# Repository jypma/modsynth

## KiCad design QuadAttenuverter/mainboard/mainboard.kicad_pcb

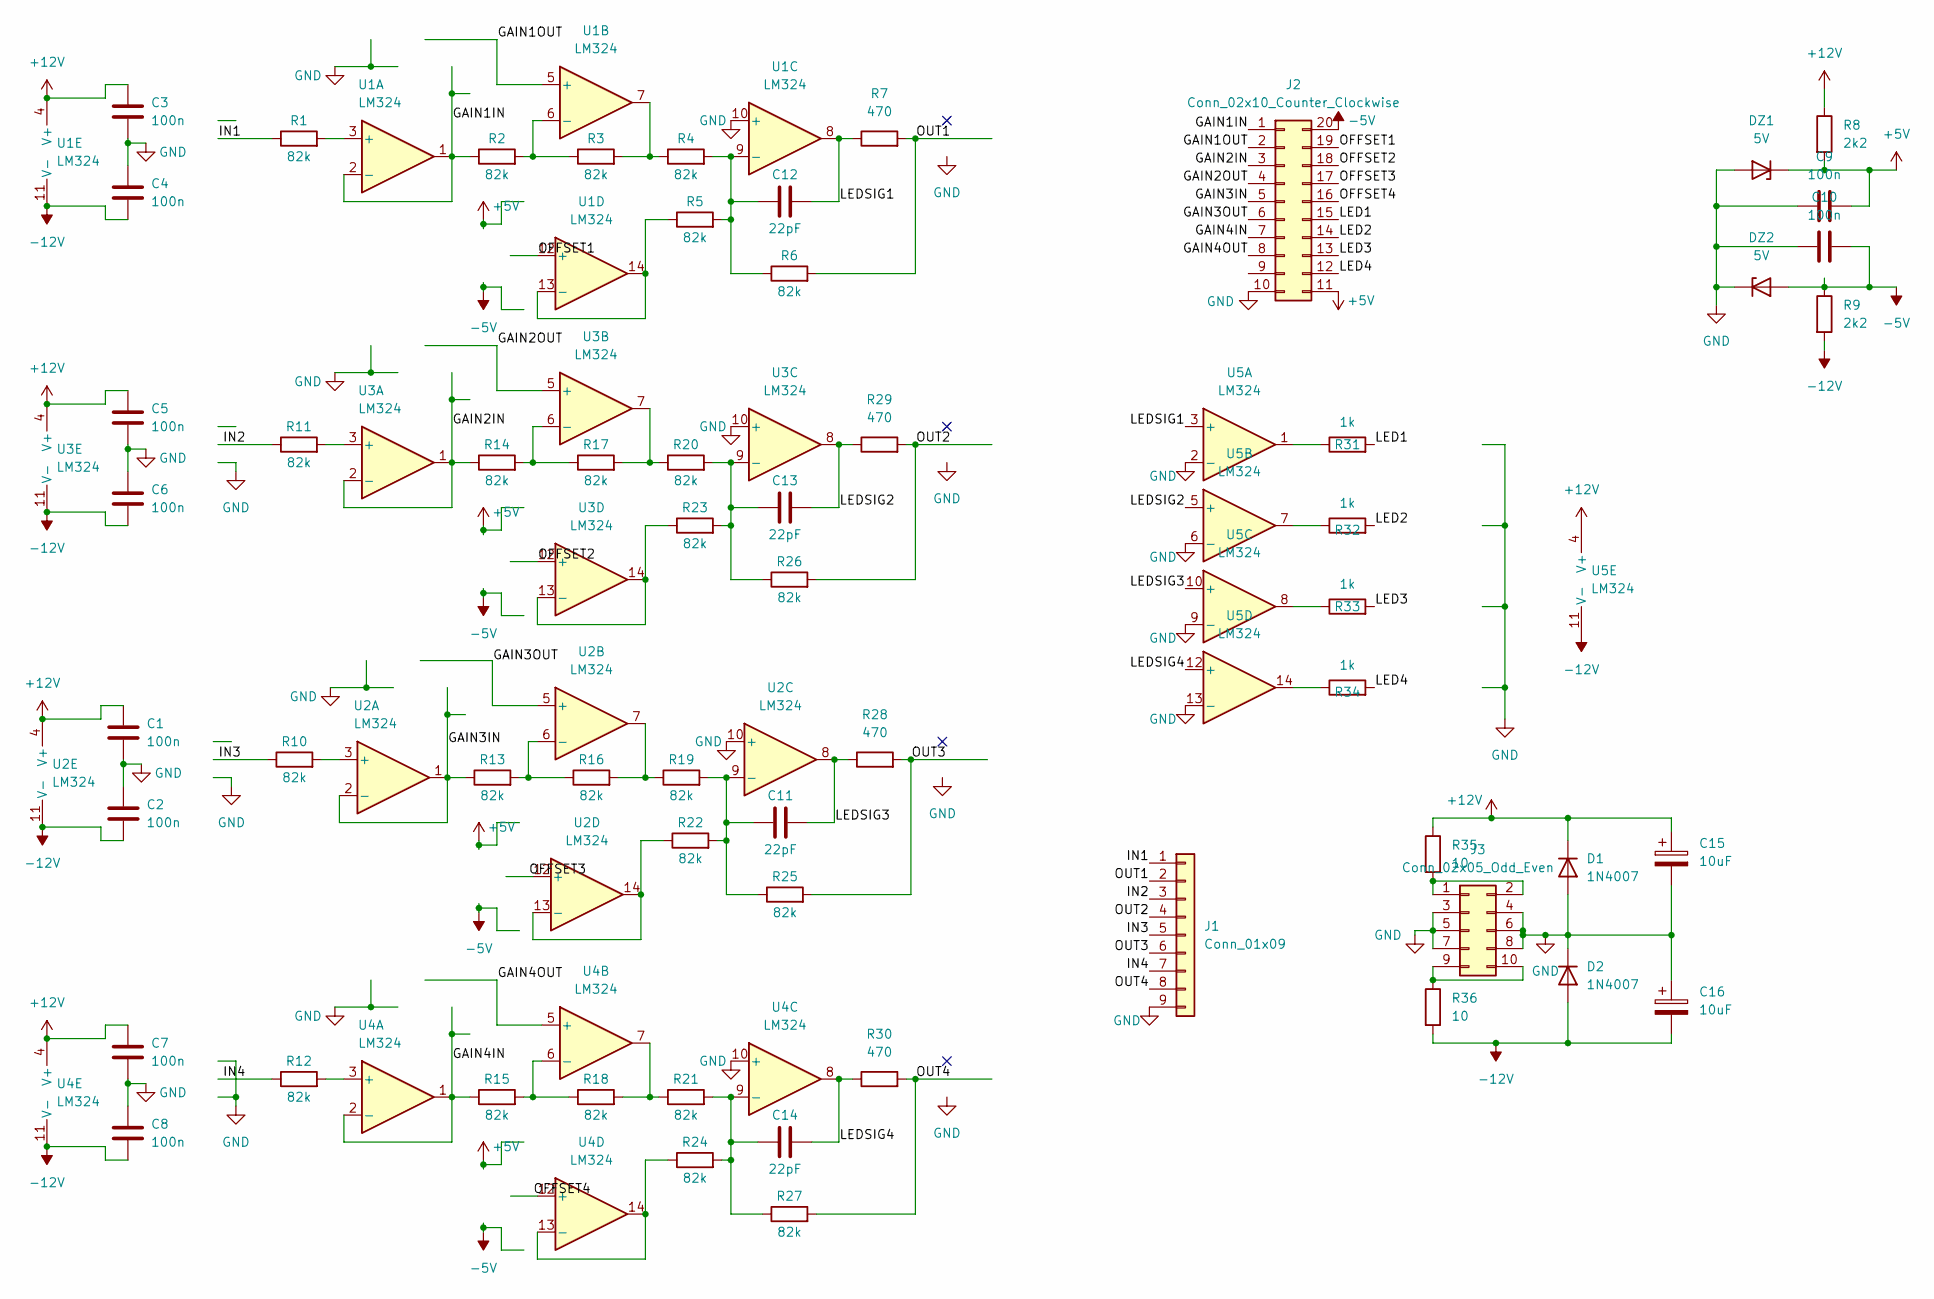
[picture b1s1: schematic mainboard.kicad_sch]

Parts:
C1, C2, C3, C4, C5, C6, C7, C8, C9, C10: 100n; C_0603_1608Metric_Pad1.08x0.95mm_HandSolder
C11, C12, C13, C14: 22pF; C_0603_1608Metric_Pad1.08x0.95mm_HandSolder
C15, C16: 10uF; CP_Radial_D5.0mm_P2.00mm
D1, D2: 1N4007; D_DO-41_SOD81_P7.62mm_Horizontal
DZ1, DZ2: 5V; D_DO-41_SOD81_P7.62mm_Horizontal
J1: Conn_01x09; PinHeader_1x09_P2.54mm_Vertical
J2: Conn_02x10_Counter_Clockwise; PinHeader_2x10_P2.54mm_Vertical
J3: Conn_02x05_Odd_Even; PinHeader_2x05_P2.54mm_Vertical
R1, R2, R3, R4, R5, R6, R10, R11, R12, R13, R14, R15, R16, R17, R18, R19, R20, R21, R22, R23, R24, R25, R26, R27: 82k; R_0603_1608Metric_Pad0.98x0.95mm_HandSolder
R7, R28, R29, R30: 470; R_0603_1608Metric_Pad0.98x0.95mm_HandSolder
R8, R9: 2k2; R_0603_1608Metric_Pad0.98x0.95mm_HandSolder
R31, R32, R33, R34: 1k; R_0603_1608Metric_Pad0.98x0.95mm_HandSolder
R35, R36: 10; R_0603_1608Metric_Pad0.98x0.95mm_HandSolder
U1, U2, U3, U4, U5: LM324; SO-14_3.9x8.65mm_P1.27mm

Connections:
+5V: C9.2, DZ1.1 (K), J2.11, R8.2
+12V: C1.1, C3.1, C5.1, C7.1, C15.1, D1.1 (K), R8.1, R35.1, U1.4 (V+), U2.4 (V+), U3.4 (V+), U4.4 (V+), U5.4 (V+)
-5V: C10.2, DZ2.2 (A), J2.20, R9.1
-12V: C2.2, C4.2, C6.2, C8.2, C16.2, D2.2 (A), R9.2, R36.2, U1.11 (V-), U2.11 (V-), U3.11 (V-), U4.11 (V-), U5.11 (V-)
/GAIN1IN: J2.1, R2.1, U1.1, U1.2 (-)
/GAIN1OUT: J2.2, U1.5 (+)
/GAIN2IN: J2.3, R14.1, U3.1, U3.2 (-)
/GAIN2OUT: J2.4, U3.5 (+)
/GAIN3IN: J2.5, R13.1, U2.1, U2.2 (-)
/GAIN3OUT: J2.6, U2.5 (+)
/GAIN4IN: J2.7, R15.1, U4.1, U4.2 (-)
/GAIN4OUT: J2.8, U4.5 (+)
/IN1: J1.1, R1.1
/IN2: J1.3, R11.1
/IN3: J1.5, R10.1
/IN4: J1.7, R12.1
/LED1: J2.15, R31.2
/LED2: J2.14, R32.2
/LED3: J2.13, R33.2
/LED4: J2.12, R34.2
/LEDSIG1: C12.2, R7.1, U1.8, U5.3 (+)
/LEDSIG2: C13.2, R29.1, U3.8, U5.5 (+)
/LEDSIG3: C11.2, R28.1, U2.8, U5.10 (+)
/LEDSIG4: C14.2, R30.1, U4.8, U5.12 (+)
/OFFSET1: J2.19, U1.12 (+)
/OFFSET2: J2.18, U3.12 (+)
/OFFSET3: J2.17, U2.12 (+)
/OFFSET4: J2.16, U4.12 (+)
/OUT1: J1.2, R6.2, R7.2
/OUT2: J1.4, R26.2, R29.2
/OUT3: J1.6, R25.2, R28.2
/OUT4: J1.8, R27.2, R30.2
GND: C1.2, C2.1, C3.2, C4.1, C5.2, C6.1, C7.2, C8.1, C9.1, C10.1, C15.2, C16.1, D1.2 (A), D2.1 (K), DZ1.2 (A), DZ2.1 (K), J1.9, J2.10, J3.3, J3.4, J3.5, J3.6, J3.7, J3.8, U1.10 (+), U2.10 (+), U3.10 (+), U4.10 (+), U5.2 (-), U5.6 (-), U5.9 (-), U5.13 (-)
unnamed: C11.1, R19.2, R22.2, R25.1, U2.9 (-)
unnamed: C12.1, R4.2, R5.2, R6.1, U1.9 (-)
unnamed: C13.1, R20.2, R23.2, R26.1, U3.9 (-)
unnamed: C14.1, R21.2, R24.2, R27.1, U4.9 (-)
unnamed: J3.1, J3.2, R35.2
unnamed: J3.9, J3.10, R36.1
unnamed: R1.2, U1.3 (+)
unnamed: R2.2, R3.1, U1.6 (-)
unnamed: R3.2, R4.1, U1.7
unnamed: R5.1, U1.13 (-), U1.14
unnamed: R10.2, U2.3 (+)
unnamed: R11.2, U3.3 (+)
unnamed: R12.2, U4.3 (+)
unnamed: R13.2, R16.1, U2.6 (-)
unnamed: R14.2, R17.1, U3.6 (-)
unnamed: R15.2, R18.1, U4.6 (-)
unnamed: R16.2, R19.1, U2.7
unnamed: R17.2, R20.1, U3.7
unnamed: R18.2, R21.1, U4.7
unnamed: R22.1, U2.13 (-), U2.14
unnamed: R23.1, U3.13 (-), U3.14
unnamed: R24.1, U4.13 (-), U4.14
unnamed: R31.1, U5.1
unnamed: R32.1, U5.7
unnamed: R33.1, U5.8
unnamed: R34.1, U5.14

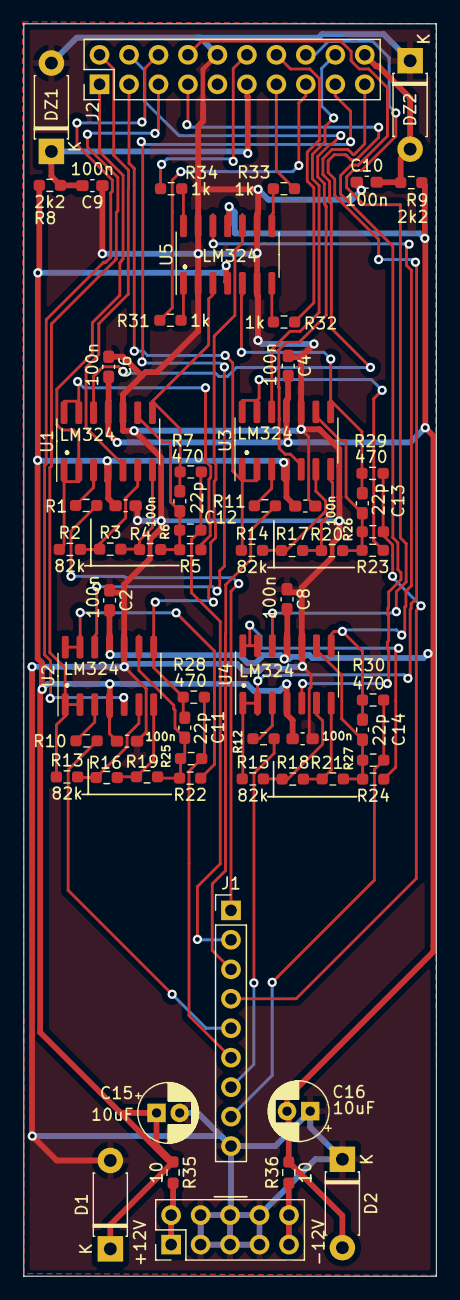
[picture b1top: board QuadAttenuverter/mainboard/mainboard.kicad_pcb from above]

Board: 2 copper layers, 35.6 x 108.0 mm, 64 parts (0 on the bottom side), 59 nets.

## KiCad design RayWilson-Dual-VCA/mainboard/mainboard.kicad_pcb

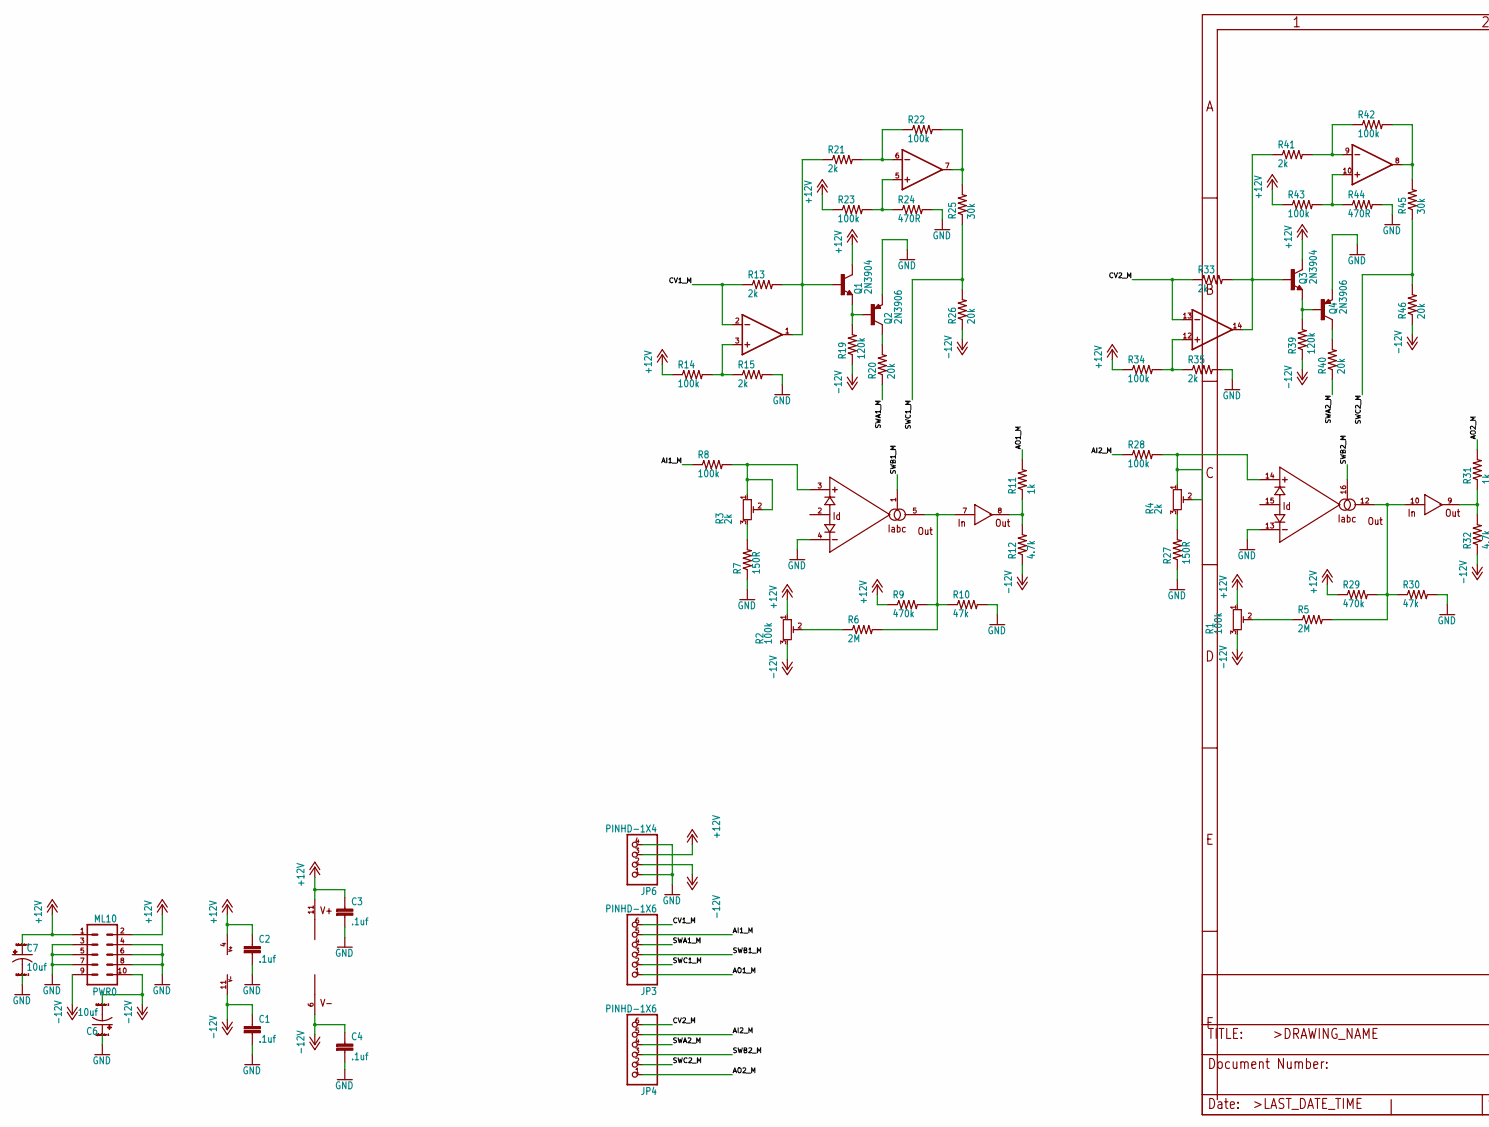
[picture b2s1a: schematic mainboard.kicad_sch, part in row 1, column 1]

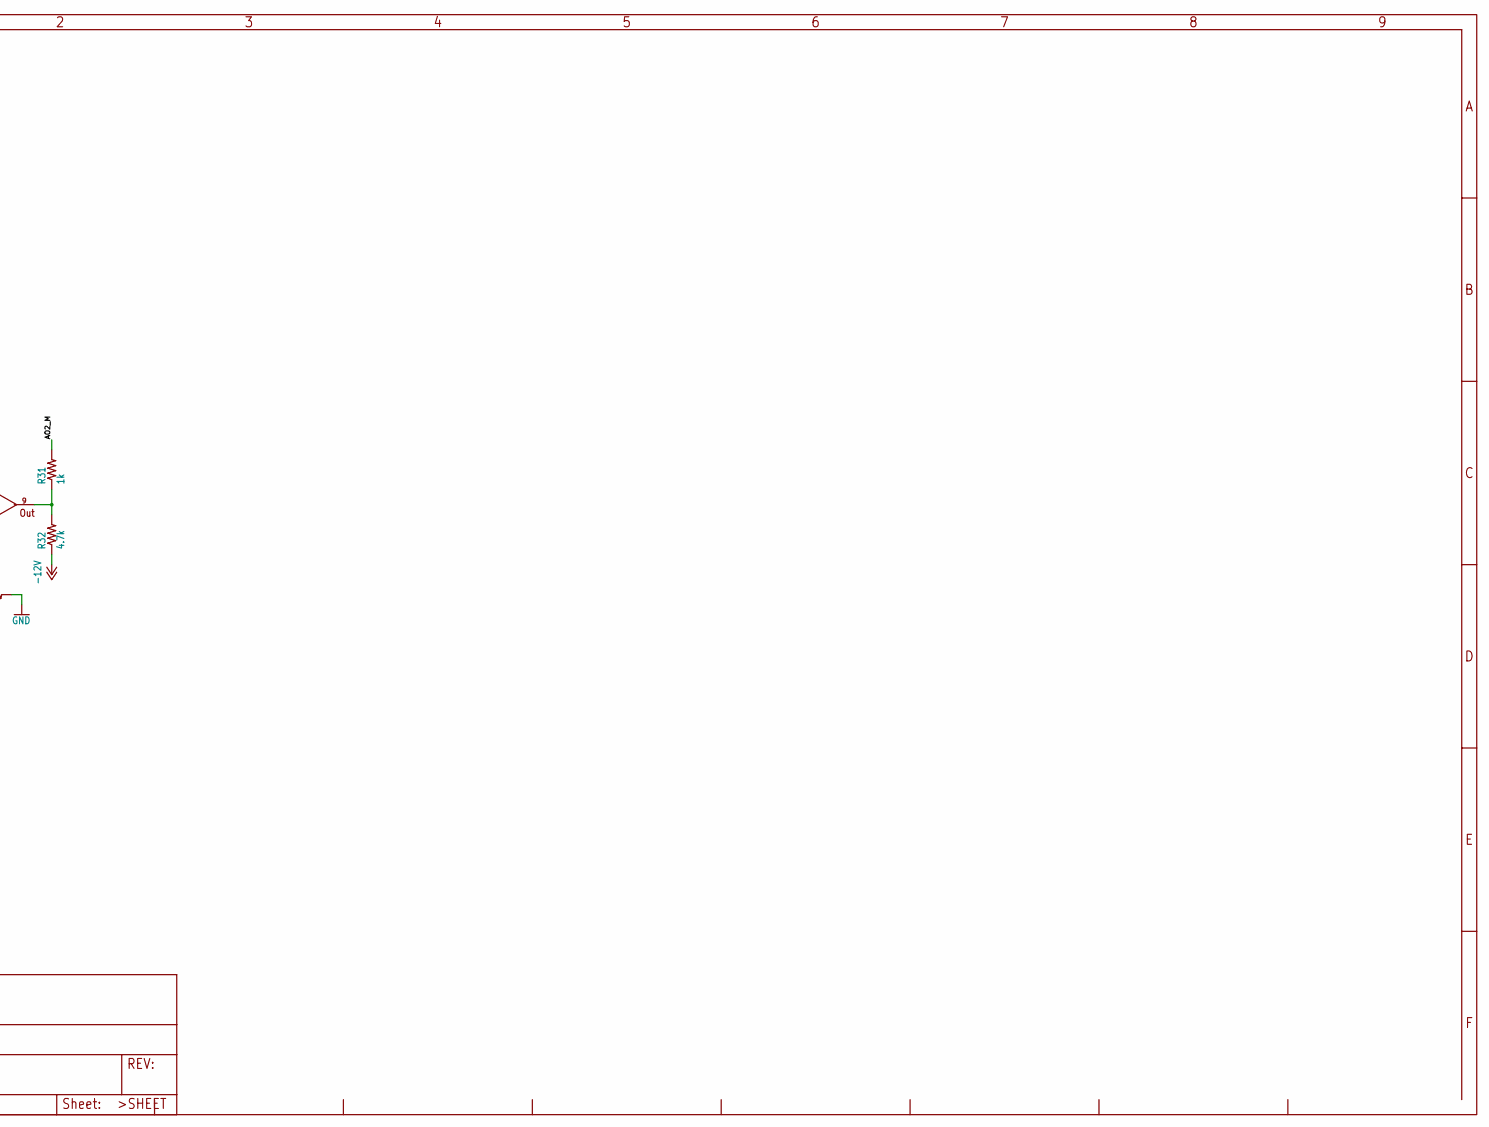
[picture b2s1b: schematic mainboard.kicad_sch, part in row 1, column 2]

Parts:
C1, C2, C3, C4: .1uf; C050-024X044
C6, C7: 10uf; E2,5-5
IC1: TL074P; SO-14_3.9x8.65mm_P1.27mm
IC2: LM13700N; SOIC-16_3.9x9.9mm_P1.27mm
JP3, JP4: PINHD-1X6; 1X06
JP6: PINHD-1X4; 1X04
PWR0: ML10
Q1, Q3: 2N3904; TO92
Q2, Q4: 2N3906; TO92
R1, R2: 100k; Potentiometer_Bourns_3296W_Vertical
R3, R4: 2k; Potentiometer_Bourns_3296W_Vertical
R5, R6: 2M; 0204_7
R7, R27: 150R; 0204_7
R8, R14, R22, R23, R28, R34, R42, R43: 100k; 0204_7
R9, R29: 470k; 0204_7
R10, R30: 47k; 0204_7
R11, R31: 1k; 0204_7
R12, R32: 4.7k; 0204_7
R13, R15, R21, R33, R35, R41: 2k; 0204_7
R19, R39: 120k; 0204_7
R20, R26, R40, R46: 20k; 0204_7
R24, R44: 470R; 0204_7
R25, R45: 30k; 0204_7

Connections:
+12V: C2.1, C3.1, C7.+, IC1.4 (V+), IC2.11 (V+), JP6.3, PWR0.1, PWR0.2, Q1.1 (C), Q3.1 (C), R1.1, R2.1, R9.1, R14.1, R23.1, R29.1, R34.1, R43.1
-12V: C1.1, C4.1, C6.-, IC1.11 (V-), IC2.6 (V-), JP6.2, PWR0.9, PWR0.10, R1.3, R2.3, R12.1, R19.1, R26.1, R32.1, R39.1, R46.1
/AI1_M: JP3.5, R8.1
/AI2_M: JP4.5, R28.1
/AO1_M: JP3.1, R11.2
/AO2_M: JP4.1, R31.2
/CV1_M: IC1.2 (-IN), JP3.6, R13.1
/CV2_M: IC1.13 (-IN), JP4.6, R33.1
/SWA1_M: JP3.4, R20.1
/SWA2_M: JP4.4, R40.1
/SWB1_M: IC2.1 (IABC), JP3.3
/SWB2_M: IC2.16 (IABC), JP4.3
/SWC1_M: JP3.2, R25.1, R26.2
/SWC2_M: JP4.2, R45.1, R46.2
GND: C1.2, C2.2, C3.2, C4.2, C6.+, C7.-, IC2.4 (-IN), IC2.13 (-IN), JP6.1, JP6.4, PWR0.3, PWR0.4, PWR0.5, PWR0.6, PWR0.7, PWR0.8, Q2.3 (E), Q4.3 (E), R7.1, R10.2, R15.2, R24.2, R27.1, R30.2, R35.2, R44.2
unnamed: IC1.1 (OUT), Q1.2 (B), R13.2, R21.1
unnamed: IC1.3 (+IN), R14.2, R15.1
unnamed: IC1.5 (+IN), R23.2, R24.1
unnamed: IC1.6 (-IN), R21.2, R22.1
unnamed: IC1.7 (OUT), R22.2, R25.2
unnamed: IC1.8 (OUT), R42.2, R45.2
unnamed: IC1.9 (-IN), R41.2, R42.1
unnamed: IC1.10 (+IN), R43.2, R44.1
unnamed: IC1.12 (+IN), R34.2, R35.1
unnamed: IC1.14 (OUT), Q3.2 (B), R33.2, R41.1
unnamed: IC2.3 (+IN), R3.1, R3.2, R8.2
unnamed: IC2.5 (OUT), IC2.7 (IN), R6.2, R9.2, R10.1
unnamed: IC2.8 (OUT), R11.1, R12.2
unnamed: IC2.9 (OUT), R31.1, R32.2
unnamed: IC2.10 (IN), IC2.12 (OUT), R5.2, R29.2, R30.1
unnamed: IC2.14 (+IN), R4.1, R4.2, R28.2
unnamed: Q1.3 (E), Q2.2 (B), R19.2
unnamed: Q2.1 (C), R20.2
unnamed: Q3.3 (E), Q4.2 (B), R39.2
unnamed: Q4.1 (C), R40.2
unnamed: R1.2, R5.1
unnamed: R2.2, R6.1
unnamed: R3.3, R7.2
unnamed: R4.3, R27.2

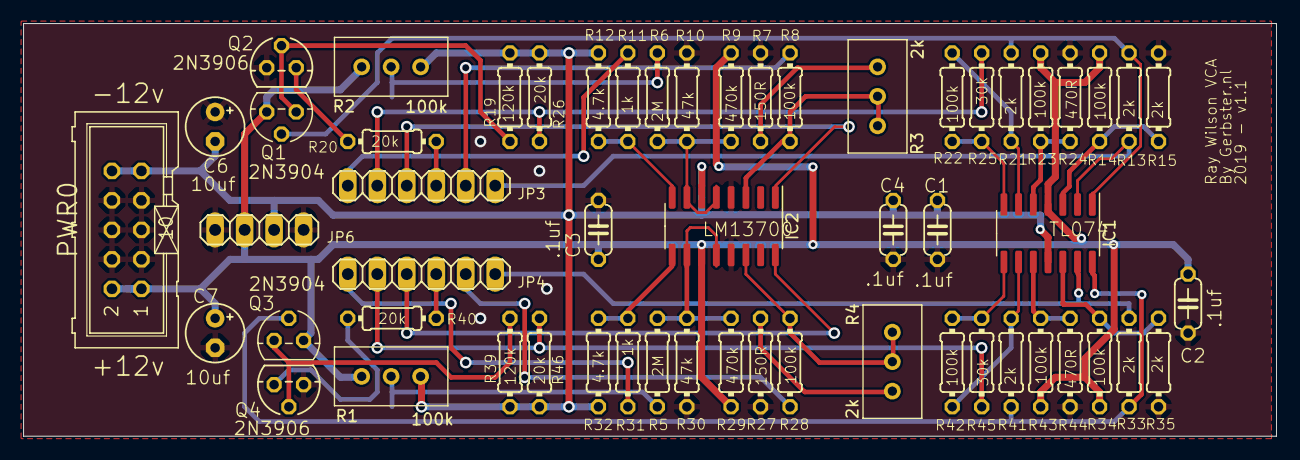
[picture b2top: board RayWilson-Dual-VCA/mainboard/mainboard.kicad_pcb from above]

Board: 2 copper layers, 108.0 x 35.6 mm, 56 parts (0 on the bottom side), 39 nets.

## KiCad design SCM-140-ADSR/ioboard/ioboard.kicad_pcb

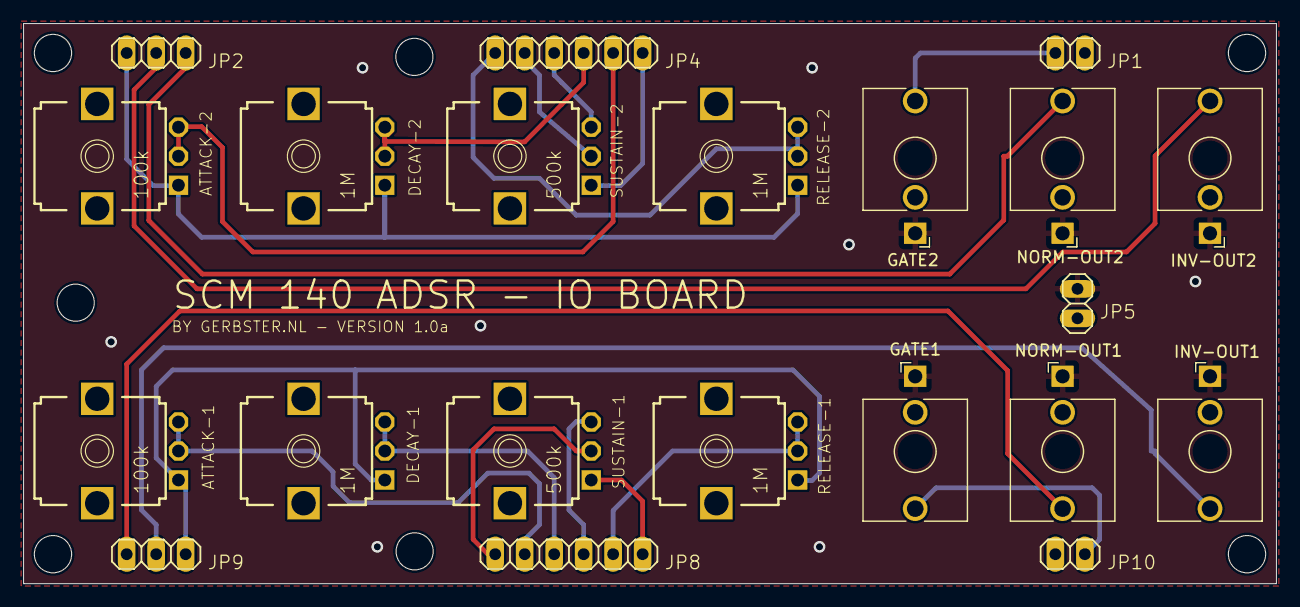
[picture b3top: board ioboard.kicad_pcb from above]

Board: 2 copper layers, 108.0 x 48.3 mm, 25 parts (0 on the bottom side), 21 nets.

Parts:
@HOLE0, @HOLE1, @HOLE2, @HOLE3: (no value)
ATTACK-1, ATTACK-2: 100k; EVUF
DECAY-1, DECAY-2: 1M; EVUF
GATE1: Input 1; Jack_3.5mm_QingPu_WQP-PJ398SM_Eagle
GATE2: Input 2; Jack_3.5mm_QingPu_WQP-PJ398SM_Eagle
INV-OUT1, INV-OUT2: Output Inv 2; Jack_3.5mm_QingPu_WQP-PJ398SM_Eagle
JP1, JP5, JP10: 1X02
JP2, JP9: 1X03
JP4, JP8: 1X06
NORM-OUT1: Output 1; Jack_3.5mm_QingPu_WQP-PJ398SM_Eagle
NORM-OUT2: Output 2; Jack_3.5mm_QingPu_WQP-PJ398SM_Eagle
RELEASE-1, RELEASE-2: 1M; EVUF
SUSTAIN-1, SUSTAIN-2: 500k; EVUF

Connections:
A1-IN: ATTACK-1.2, ATTACK-1.3, JP8.5
A2-IN: ATTACK-2.2, ATTACK-2.3, JP4.5
C1-OUT: ATTACK-1.1, DECAY-1.1, JP9.1, RELEASE-1.1
C2-OUT: ATTACK-2.1, DECAY-2.1, JP2.1, RELEASE-2.1
D1-IN: DECAY-1.2, DECAY-1.3, JP8.4
D2-IN: DECAY-2.2, DECAY-2.3, JP4.4
GATE-1: GATE1.TIP, JP10.2
GATE-2: GATE2.TIP, JP1.2
GND: GATE1.GND1, GATE2.GND1, INV-OUT1.GND1, INV-OUT2.GND1, JP5.1, NORM-OUT1.GND1, NORM-OUT2.GND1
INV-OUT-1: INV-OUT1.TIP, JP9.2
INV-OUT-2: INV-OUT2.TIP, JP2.2
NORM-OUT-1: JP9.3, NORM-OUT1.TIP
NORM-OUT-2: JP2.3, NORM-OUT2.TIP
R1-IN: JP8.2, RELEASE-1.2, RELEASE-1.3
R2-IN: JP4.1, RELEASE-2.2, RELEASE-2.3
S1-A: JP8.3, SUSTAIN-1.3
S1-B: JP8.1, SUSTAIN-1.1
S1-W: JP8.6, SUSTAIN-1.2
S2-A: JP4.3, SUSTAIN-2.3
S2-B: JP4.6, SUSTAIN-2.1
S2-W: JP4.2, SUSTAIN-2.2

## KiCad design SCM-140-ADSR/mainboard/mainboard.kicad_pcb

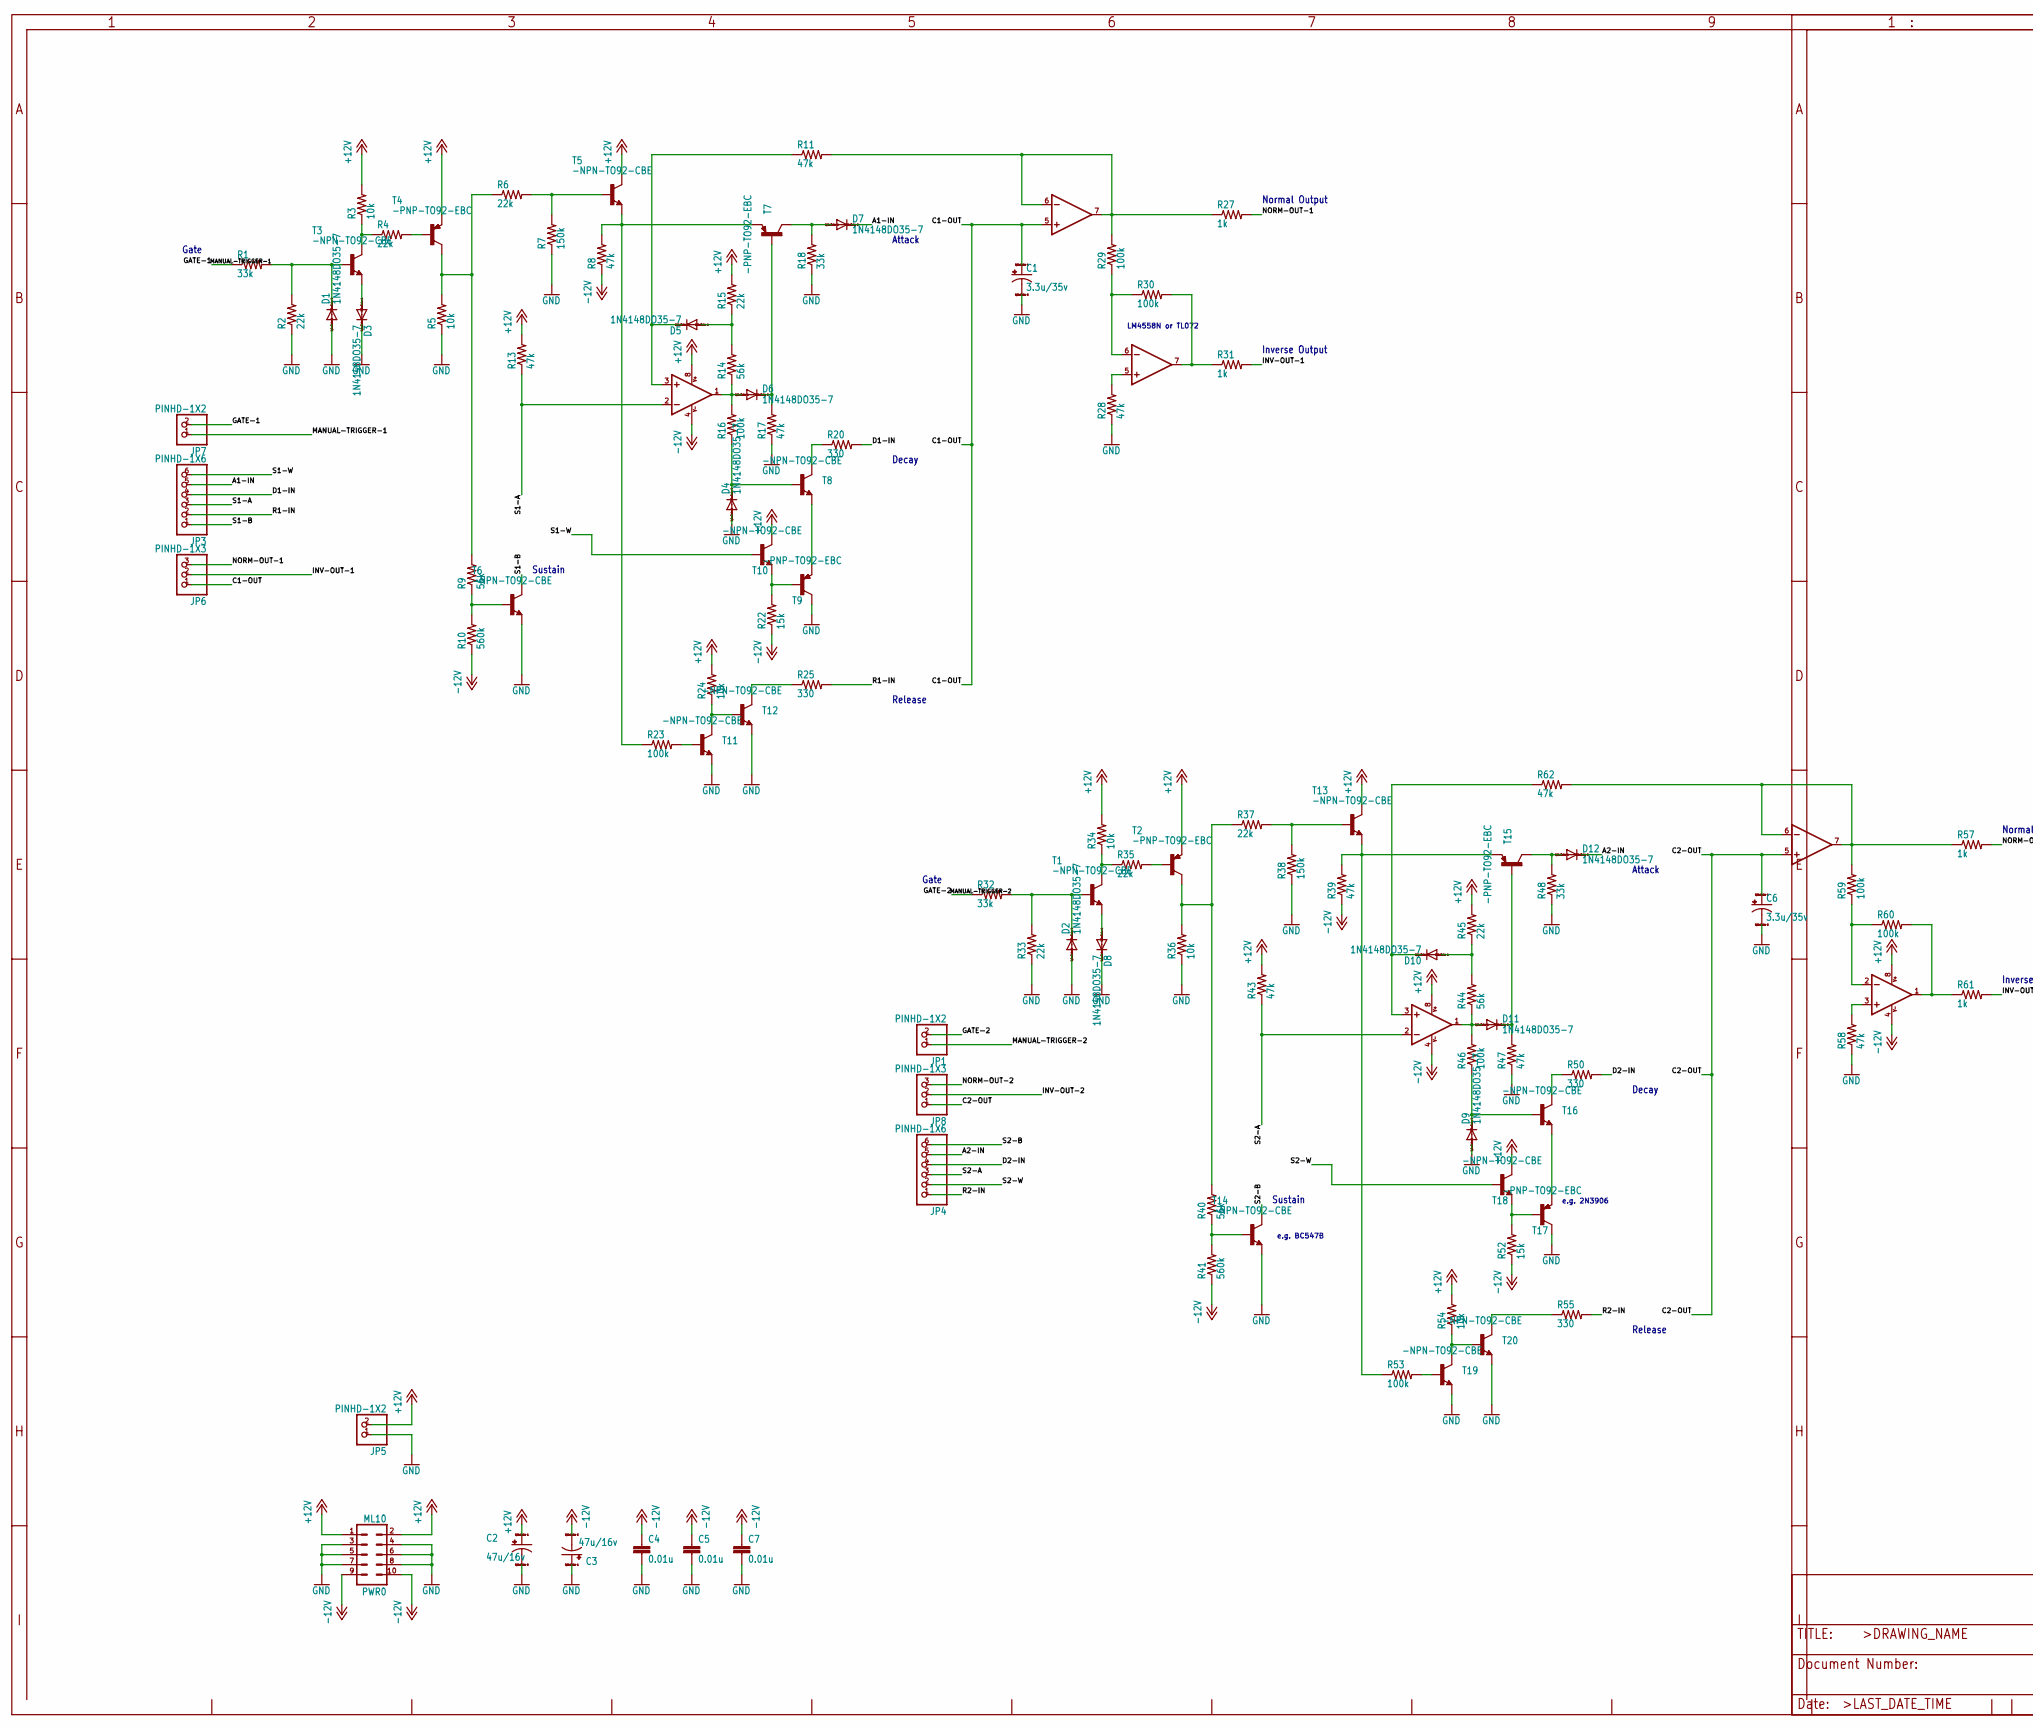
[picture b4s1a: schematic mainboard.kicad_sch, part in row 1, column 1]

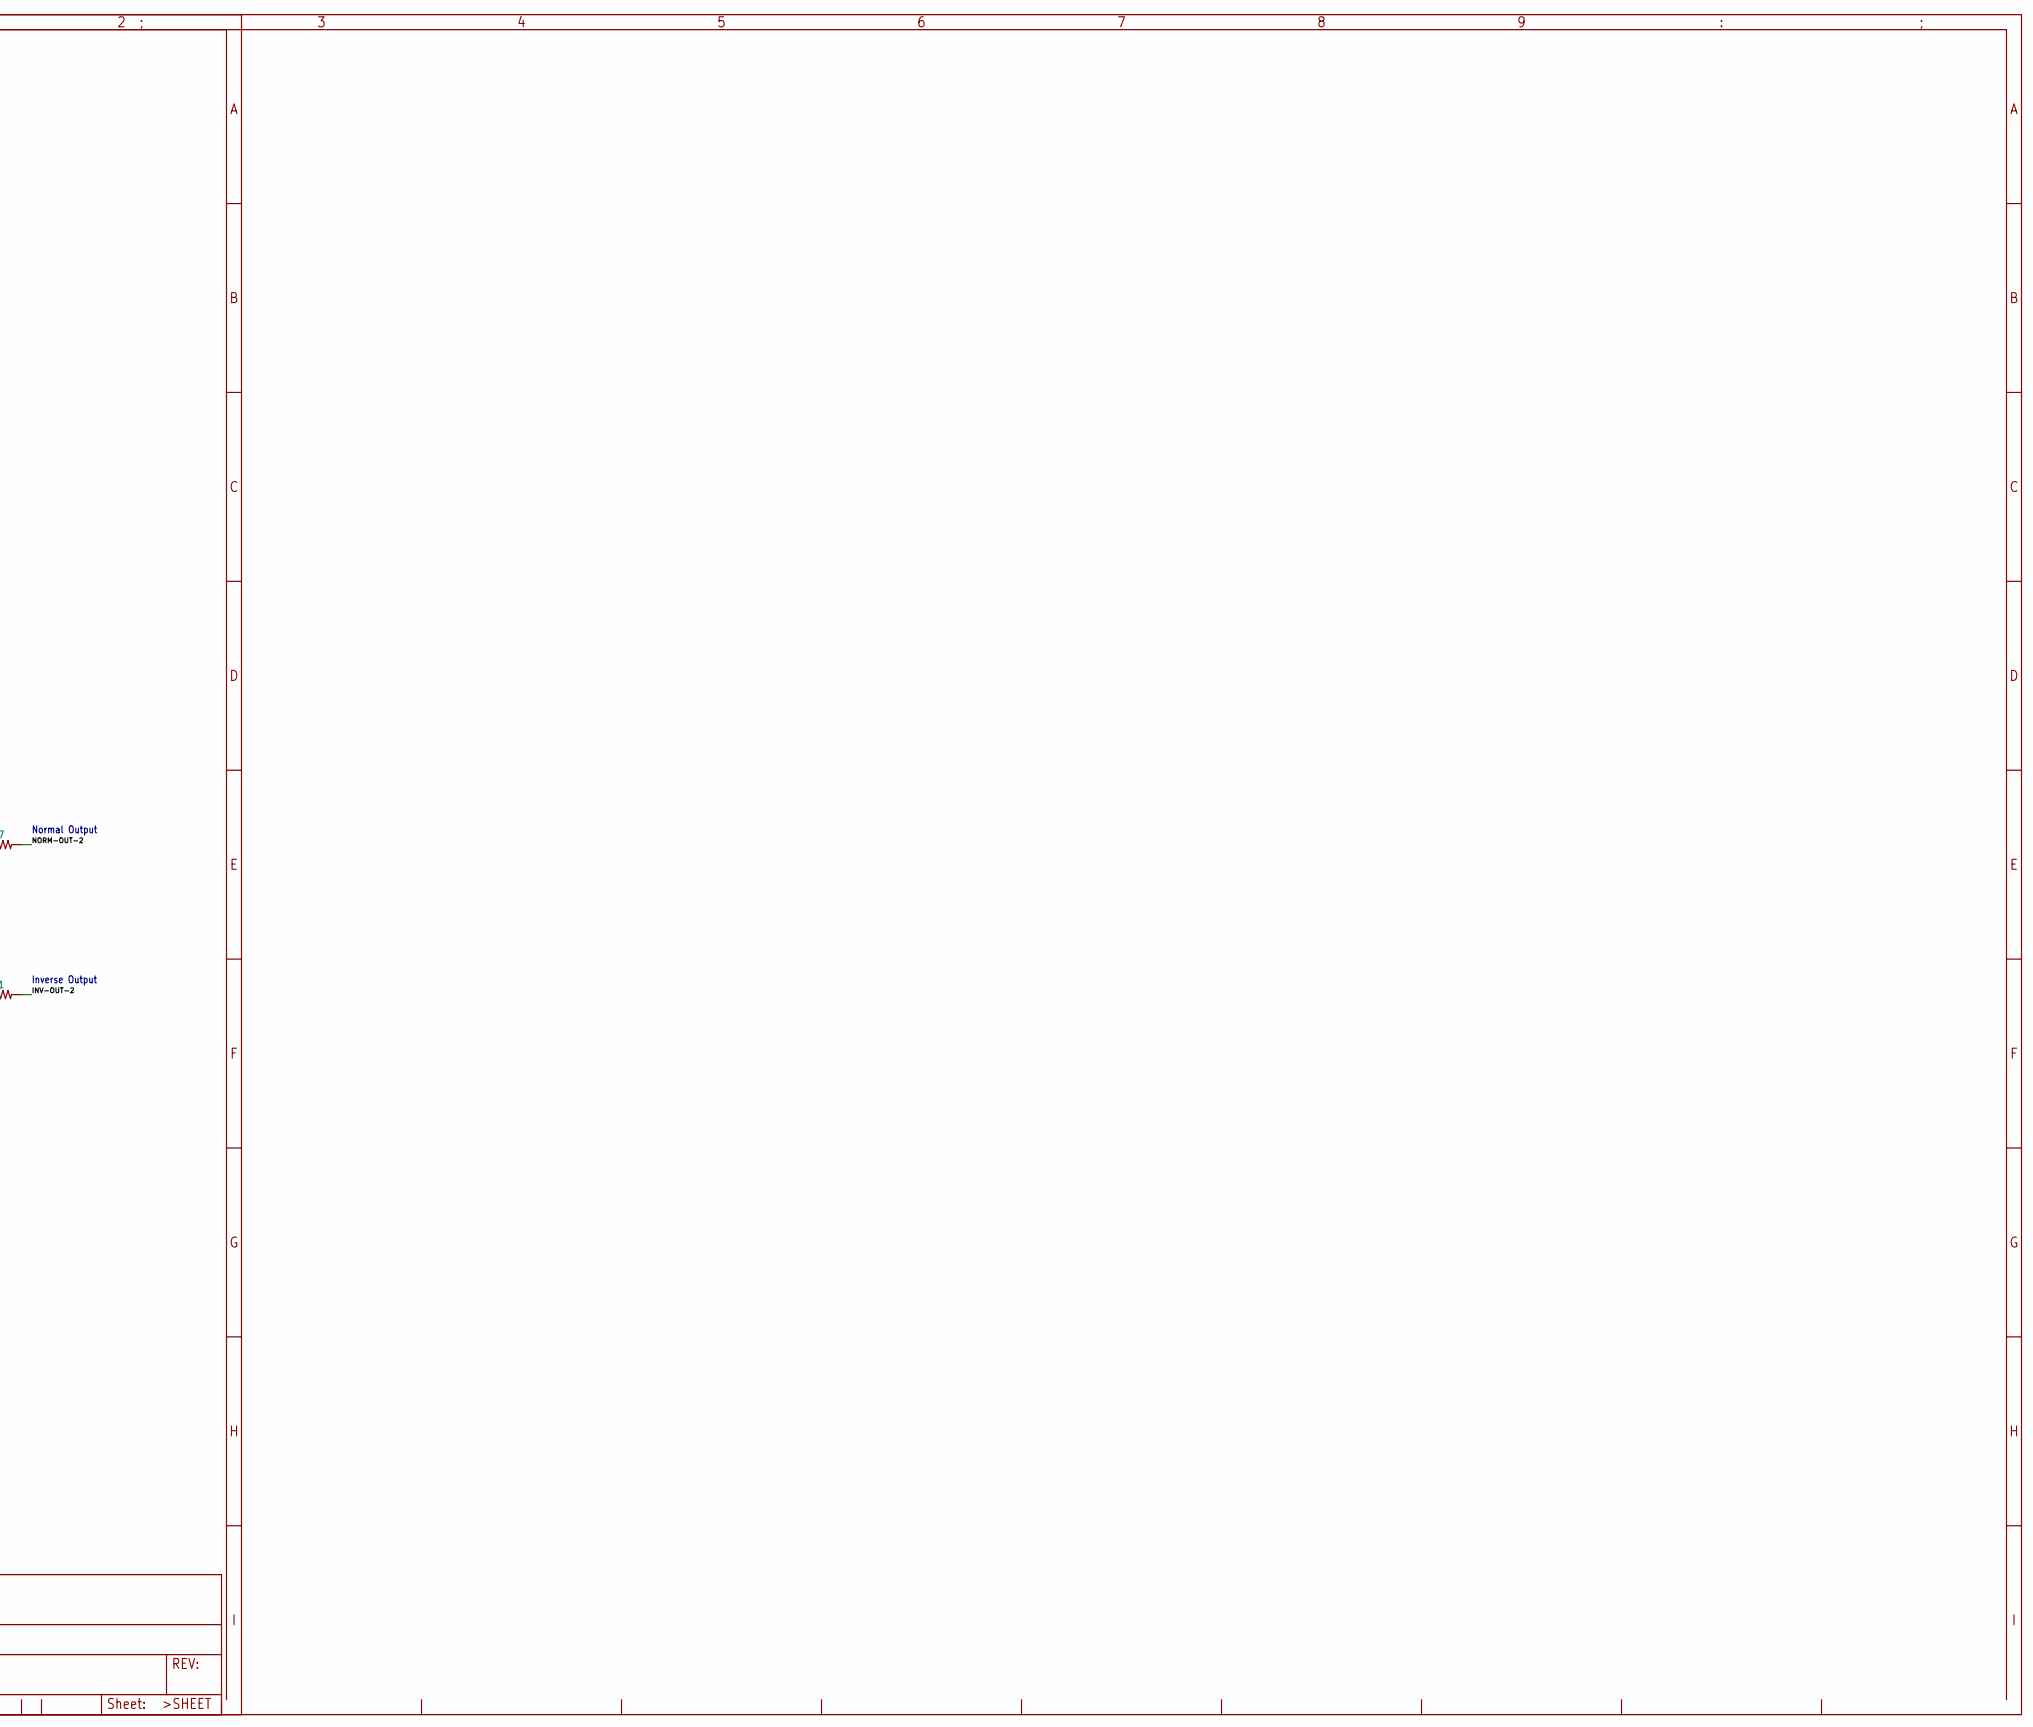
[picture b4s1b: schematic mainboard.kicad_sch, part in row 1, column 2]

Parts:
C1, C6: 3.3u/35v; E2,5-5
C2, C3: 47u/16v; E2,5-5
C4, C5, C7: 0.01u; C025-024X044
D1, D2, D3, D4, D5, D6, D7, D8, D9, D10, D11, D12: 1N4148DO35-7; DO35-7
IC1, IC2, IC3: 4558N; DIL08
JP1, JP5, JP7: PINHD-1X2; 1X02
JP3, JP4: PINHD-1X6; 1X06
JP6, JP8: PINHD-1X3; 1X03
PWR0: ML10
R1, R18, R32, R48: 33k; 0204_7
R2, R4, R6, R15, R33, R35, R37, R45: 22k; 0204_7
R3, R5, R24, R34, R36, R54: 10k; 0204_7
R7, R38: 150k; 0204_7
R8, R11, R13, R17, R28, R39, R43, R47, R58, R62: 47k; 0204_7
R9, R14, R40, R44: 56k; 0204_7
R10, R41: 560k; 0204_7
R16, R23, R29, R30, R46, R53, R59, R60: 100k; 0204_7
R20, R25, R50, R55: 330; 0204_7
R22, R52: 15k; 0204_7
R27, R31, R57, R61: 1k; 0204_7
T1, T3, T5, T6, T8, T10, T11, T12, T13, T14, T16, T18, T19, T20: -NPN-TO92-CBE; TO92-CBE
T2, T4, T7, T9, T15, T17: -PNP-TO92-EBC; TO92-EBC

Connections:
+12V: C2.+, IC1.8 (V+), IC2.8 (V+), IC3.8 (V+), JP5.2, PWR0.1, PWR0.2, R3.2, R13.2, R15.2, R24.2, R34.2, R43.2, R45.2, R54.2, T2.E, T4.E, T5.C, T10.C, T13.C, T18.C
-12V: C3.-, C4.1, C5.1, C7.1, IC1.4 (V-), IC2.4 (V-), IC3.4 (V-), PWR0.9, PWR0.10, R8.1, R10.1, R22.1, R39.1, R41.1, R52.1
A1-IN: D7.C, JP3.5
A2-IN: D12.C, JP4.5
C1-OUT: C1.+, IC1.5 (+IN), JP6.1
C2-OUT: C6.+, IC2.5 (+IN), JP8.1
D1-IN: JP3.4, R20.2
D2-IN: JP4.4, R50.2
GATE-1: JP7.2, R1.1
GATE-2: JP1.2, R32.1
GND: C1.-, C2.-, C3.+, C4.2, C5.2, C6.-, C7.2, D1.A, D2.A, D3.C, D4.A, D8.C, D9.A, JP5.1, PWR0.3, PWR0.4, PWR0.5, PWR0.6, PWR0.7, PWR0.8, R2.1, R5.1, R7.1, R17.1, R18.1, R28.1, R33.1, R36.1, R38.1, R47.1, R48.1, R58.1, T6.E, T9.C, T11.E, T12.E, T14.E, T17.C, T19.E, T20.E
INV-OUT-1: JP6.2, R31.2
INV-OUT-2: JP8.2, R61.2
MANUAL-TRIGGER-1: D1.C, JP7.1, R1.2, R2.2, T3.B
MANUAL-TRIGGER-2: D2.C, JP1.1, R32.2, R33.2, T1.B
unnamed: D5.C, IC1.3 (+IN), R11.1
unnamed: D3.A, T3.E
unnamed: R3.1, R4.1, T3.C
unnamed: R4.2, T4.B
unnamed: R5.2, R6.1, R9.2, T4.C
unnamed: R8.2, R23.1, T5.E, T7.E
unnamed: R6.2, R7.2, T5.B
unnamed: R9.1, R10.2, T6.B
unnamed: D6.A, IC1.1 (OUT), R14.1, R16.2
unnamed: D4.C, R16.1, T8.B
unnamed: D5.A, R14.2, R15.1
unnamed: IC1.6 (-IN), IC1.7 (OUT), R11.2, R27.1, R29.2
unnamed: D7.A, R18.2, T7.C
unnamed: D6.C, R17.2, T7.B
unnamed: IC3.6 (-IN), R29.1, R30.1
unnamed: R20.1, T8.C
unnamed: R22.2, T9.B, T10.E
unnamed: T8.E, T9.E
unnamed: R23.2, T11.B
unnamed: R24.1, T11.C, T12.B
unnamed: R25.1, T12.C
unnamed: IC3.7 (OUT), R30.2, R31.1
unnamed: D8.A, T1.E
unnamed: IC3.5 (+IN), R28.2
unnamed: R34.1, R35.1, T1.C
unnamed: R35.2, T2.B
unnamed: R36.2, R37.1, R40.2, T2.C
unnamed: R39.2, R53.1, T13.E, T15.E
unnamed: R37.2, R38.2, T13.B
unnamed: R40.1, R41.2, T14.B
unnamed: D11.A, IC2.1 (OUT), R44.1, R46.2
unnamed: D9.C, R46.1, T16.B
unnamed: D10.A, R44.2, R45.1
unnamed: IC2.6 (-IN), IC2.7 (OUT), R57.1, R59.2, R62.2
unnamed: D11.C, R47.2, T15.B
unnamed: D12.A, R48.2, T15.C
unnamed: R50.1, T16.C
unnamed: R52.2, T17.B, T18.E
unnamed: T16.E, T17.E
unnamed: R53.2, T19.B
unnamed: R54.1, T19.C, T20.B
unnamed: R55.1, T20.C
unnamed: IC3.2 (-IN), R59.1, R60.1
unnamed: IC3.1 (OUT), R60.2, R61.1
unnamed: IC3.3 (+IN), R58.2
unnamed: D10.C, IC2.3 (+IN), R62.1
NORM-OUT-1: JP6.3, R27.2
NORM-OUT-2: JP8.3, R57.2
R1-IN: JP3.2, R25.2
R2-IN: JP4.1, R55.2
S1-A: IC1.2 (-IN), JP3.3, R13.1
S1-B: JP3.1, T6.C
S1-W: JP3.6, T10.B
S2-A: IC2.2 (-IN), JP4.3, R43.1
S2-B: JP4.6, T14.C
S2-W: JP4.2, T18.B

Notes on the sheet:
Attack
e.g. 2N3906
Decay
Normal Output
Sustain
Inverse Output
Release
LM4558N or TL072
Gate
e.g. BC547B

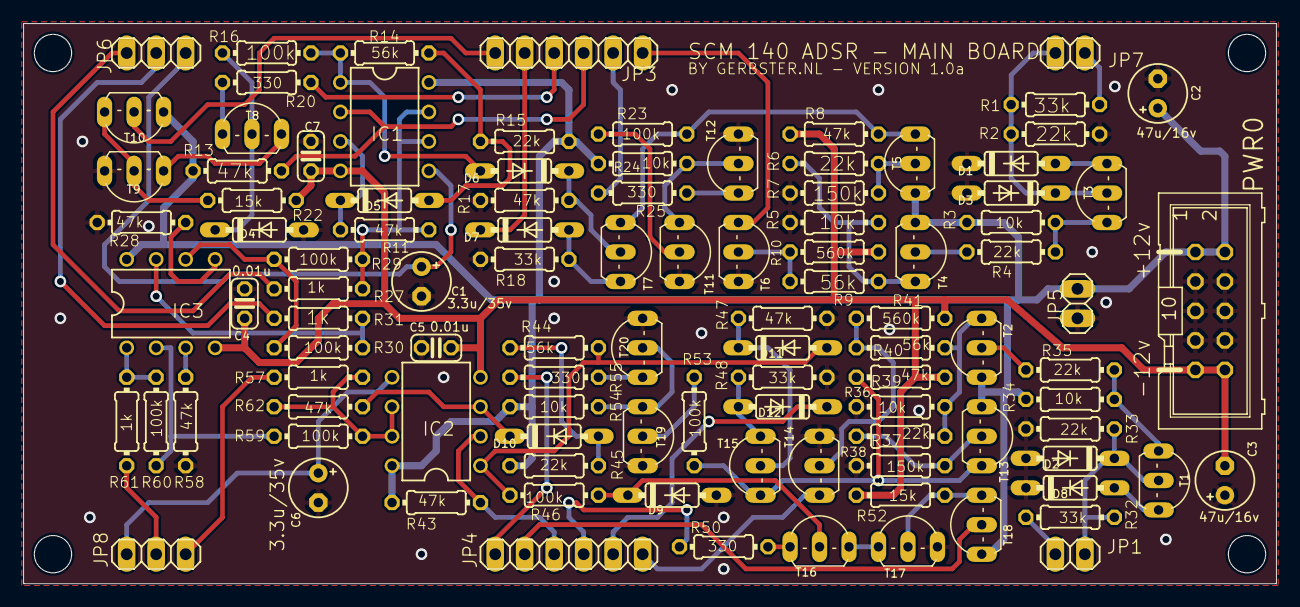
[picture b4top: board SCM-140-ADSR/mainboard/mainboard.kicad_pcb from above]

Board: 2 copper layers, 108.0 x 48.3 mm, 108 parts (0 on the bottom side), 71 nets.

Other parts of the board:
@HOLE0, @HOLE1, @HOLE2, @HOLE3: (no value)
